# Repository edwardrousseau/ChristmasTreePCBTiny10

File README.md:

# Christmas tree with LEDs and Attiny4-5-9-10

## Getting Started

This is a christmas tree ornament that uses an Attiny and 3 LEDs. The power is supplied by a CR2032 battery.

## Requirements

* Arduino IDE version 1.8.3 (The attine10 core is not working on higher versions)
* [ATtiny10Core](https://github.com/technoblogy/attiny10core)
* USBASP programmer(Need recent firmware, will probably require an update if bought from eBay)

See [here](http://www.technoblogy.com/show?1YQY) to learn how to install the required software and program the MCU.

## Building
### Programming

The PCB does not include a programming port. It is possible to use an external programmer with a socket, or use one of the PCB as the programmer. 
To do it:

 1. Solder wires to one PCB as seen in the images folder (including RESET on the backside, 5 wires in total)
 2. Plug the wires in one end of the programmer's cable
 3. Disconnect the cable from the programmer
 4. Place the IC on the PCB, at the right place and in the right direction, and hold it with one hand
 5. With the other hand, plug the wire in the programmer
 6. Program with the Arduino IDE
 7. Disconnect the programmer's cable

### Assembling
* Start with the MCU.
* Continue with the leds (D*) and the resistors (R*). For the leds, the small green dot is the negative side and it goes in the "white box".
* Solder the battery holder. The + side is at the top.

## BOM

* PCB (Printed Circuit Boards, order from OSHPark or another supplier)
* MCU (Attiny4-5-9-10)
* 3 * 0805 1kOhm resistors
* 3 * 0805 LED (different colors)
* 2032 battery holder (with distance between pins of 20mm)

## Possible improvements
* Real pseudo-random LEDs pattern
* Add a small programming port
* Use a smaller battery so it is smaller than the board

## Author

* **Edward Rousseau** - *Initial work* - [Edward Rousseau](https://github.com/edwardrousseau)

## License

This project is licensed under the GPLv3 - see the [LICENSE](LICENSE) file for details

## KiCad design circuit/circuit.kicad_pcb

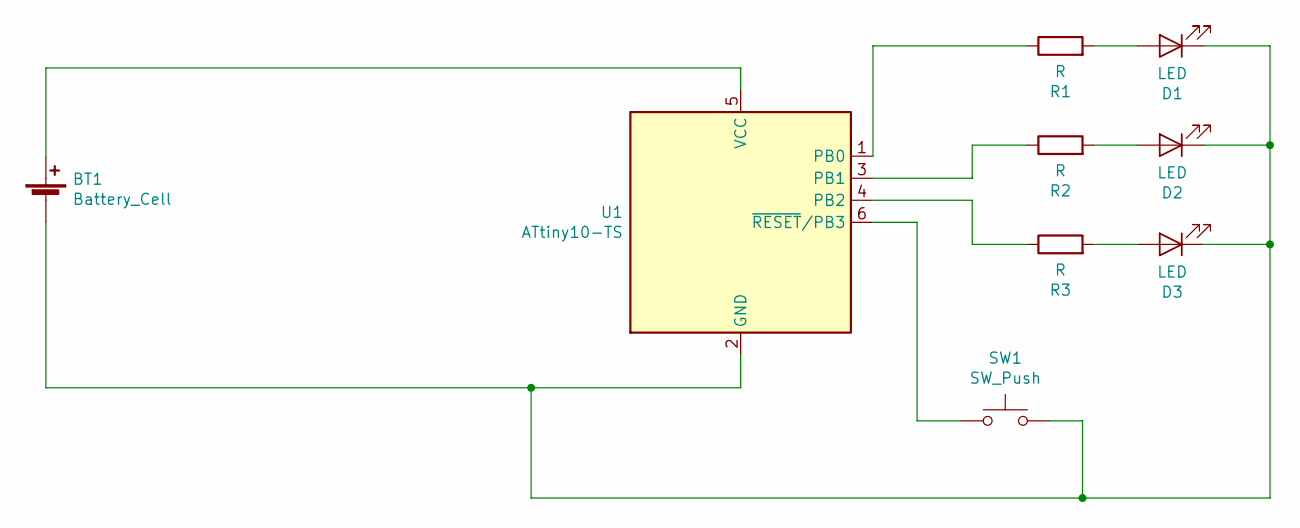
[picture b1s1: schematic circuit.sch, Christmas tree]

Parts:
BT1: Battery_Cell; battery
D1, D2, D3: LED; LED_0805_2012Metric_Pad1.15x1.40mm_HandSolder
R1, R2, R3: R; R_0805_2012Metric_Pad1.15x1.40mm_HandSolder
SW1: SW_Push; SW_SPST_TL3342
U1: ATtiny10-TS; SOT-23-6

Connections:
unnamed: BT1.1 (+), U1.5 (VCC)
unnamed: BT1.2 (-), D1.1 (K), D2.1 (K), D3.1 (K), SW1.2, U1.2 (GND)
unnamed: D1.2 (A), R1.2
unnamed: D2.2 (A), R2.2
unnamed: D3.2 (A), R3.2
unnamed: R1.1, U1.1 (PB0)
unnamed: R2.1, U1.3 (PB1)
unnamed: R3.1, U1.4 (PB2)
unnamed: SW1.1, U1.6 (~RESET~/PB3)

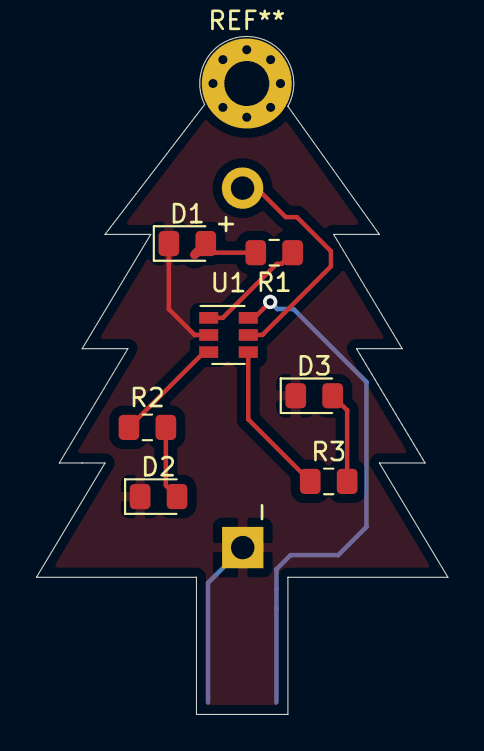
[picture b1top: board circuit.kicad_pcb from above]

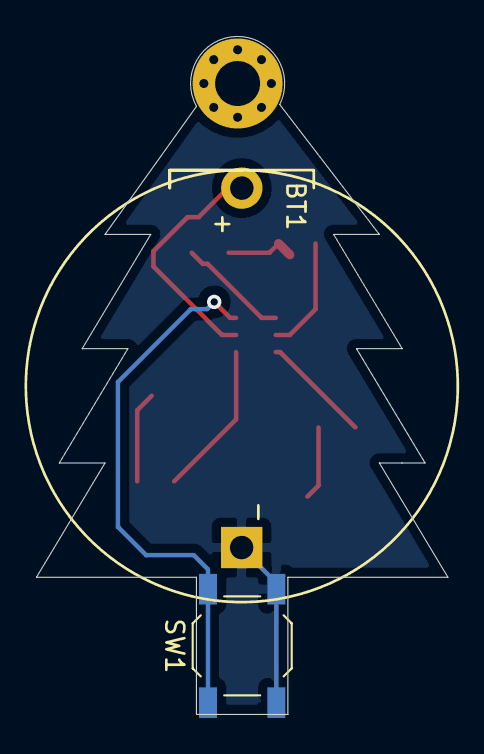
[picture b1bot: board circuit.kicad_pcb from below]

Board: 2 copper layers, 22.9 x 37.7 mm, 9 parts (2 on the bottom side), 9 nets.

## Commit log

2020-12-20 Update arduino_program.ino
    Add comments and GPLv3 license
2020-12-20 Update schematic info and use the good version
    Update schematic info and use the good version of the files, delete old Gerbers
2020-12-20 Correct battery polarity
    Correct battery polarity, update PCB info
2020-12-20 Add Gerbers files and images
2020-12-20 Add images
    Add images
2020-12-21 Progrmming images
2020-12-21 PDF schematic

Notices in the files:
circuit/circuit.kicad_pcb:
GPLv3 license, see LICENSE file
circuit/circuit.sch:
Licensed under GPLv3, see LICENSE file
